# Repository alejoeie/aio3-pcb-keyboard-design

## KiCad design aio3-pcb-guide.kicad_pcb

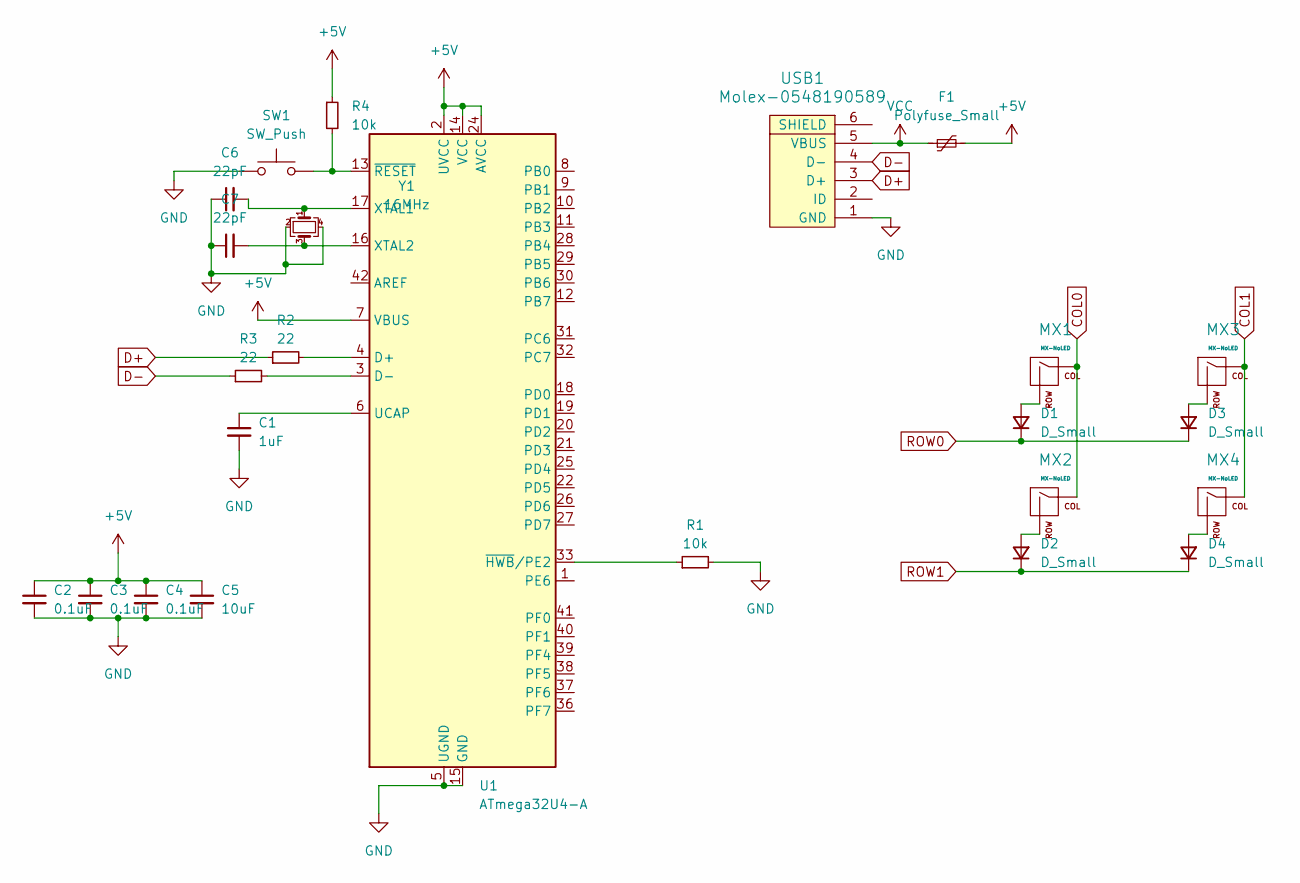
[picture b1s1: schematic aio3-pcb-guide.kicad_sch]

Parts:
C1: 1uF; C_0805_2012Metric
C2, C3, C4: 0.1uF; C_0805_2012Metric
C5: 10uF; C_0805_2012Metric
C6, C7: 22pF; C_0805_2012Metric
D1, D2, D3, D4: D_Small; D_SOD-123
F1: Polyfuse_Small; Fuse_1206_3216Metric
MX1, MX2, MX3, MX4: MX-NoLED; MX-1U-NoLED
R1, R4: 10k; R_0805_2012Metric
R2, R3: 22; R_0805_2012Metric
SW1: SW_Push; Reset_Pretty
U1: ATmega32U4-A; TQFP-44_10x10mm_P0.8mm
USB1: Molex-0548190589
Y1: 16MHz; Crystal_SMD_3225-4Pin_3.2x2.5mm

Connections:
+5V: C2.1, C3.1, C4.1, C5.1, F1.2, R4.1, U1.2 (UVCC), U1.7 (VBUS), U1.14 (VCC), U1.24 (AVCC), U1.34 (VCC), U1.44 (AVCC)
COL0: MX1.1 (COL), MX2.1 (COL)
COL1: MX3.1 (COL), MX4.1 (COL)
D+: R2.1, USB1.3 (D+)
D-: R3.1, USB1.4 (D-)
GND: C1.2, C2.2, C3.2, C4.2, C5.2, C6.1, C7.1, R1.2, SW1.1, U1.5 (UGND), U1.15 (GND), U1.23 (GND), U1.35 (GND), U1.43 (GND), USB1.1 (GND), Y1.2, Y1.4
unnamed: D1.2 (A), MX1.2 (ROW)
unnamed: D2.2 (A), MX2.2 (ROW)
unnamed: D3.2 (A), MX3.2 (ROW)
unnamed: D4.2 (A), MX4.2 (ROW)
unnamed: R2.2, U1.4 (D+)
unnamed: R3.2, U1.3 (D-)
unnamed: C1.1, U1.6 (UCAP)
unnamed: C6.2, U1.17 (XTAL1), Y1.1
unnamed: C7.2, U1.16 (XTAL2), Y1.3
unnamed: R1.1, U1.33 (~HWB/PE2)
unnamed: R4.2, SW1.2, U1.13 (~RESET)
ROW0: D1.1 (K), D3.1 (K)
ROW1: D2.1 (K), D4.1 (K)
VCC: F1.1, USB1.5 (VBUS)

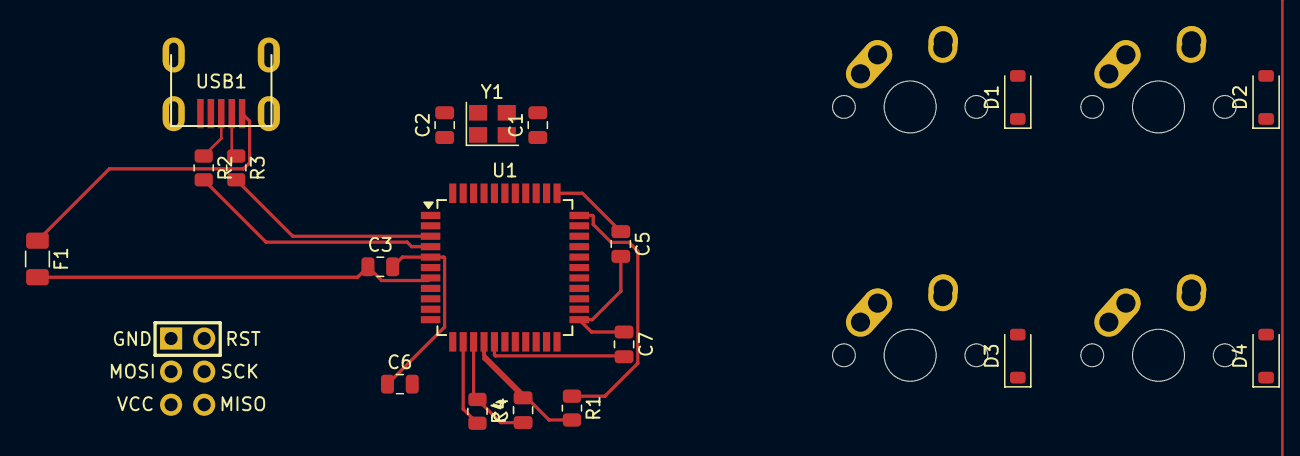
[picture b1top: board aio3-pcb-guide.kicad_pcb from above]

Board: 2 copper layers, 24 parts (0 on the bottom side), 20 nets.

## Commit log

2024-06-17 Add schematic and physical layout design
    Adding basic structures for schematics and physical layout of the keyboard.
2024-06-17 Add submodules for switches and USB connector.
2024-06-17 Add footprint and schematic libraries
    Implemented schematics and routing stage for layout
